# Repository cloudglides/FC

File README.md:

<h1 align="center">
  FC
  <br>
</h1>
<h4 align="center">
An STM32F405 flight controller
</h4>
<div align="center">

</div>
<p align="center">
  <a href="#key-features">Key Features</a> •
  <a href="#pcb">PCB</a> •
  <a href="#credits">Credits</a>
</p>

<p>&nbsp;</p>

# FC

FC is a 39 × 39 mm flight controller for multirotors, built around the STM32F405RGT6, with a 30.5 × 30.5 mm M3 mounting pattern.

it has a BMI270 gyro, a BMP388 barometer, 16 MB of blackbox flash and a 2S–6S power stage on one 4-layer board. connectors are JST-SH for a 4-in-1 ESC, receiver, HD VTX and GPS, plus USB-C.

to build your own, grab the KiCad files in `pcb/`, check the schematic and BOM, and send the Gerber files in `production/` to your preferred PCB manufacturer. the MCU can be flashed over USB (hold BOOT while plugging in) or through the SWD pads.

## Key Features

* **STM32F405RGT6** MCU, 168 MHz Cortex-M4
* **BMI270** 6-axis IMU on SPI
* **BMP388** barometer on I2C
* **W25Q128** 16 MB blackbox flash
* **2S–6S input** with an AP63205 5 V / 2 A buck and AP2112K 3.3 V regulator
* **USB-C** with ESD protection using USBLC6-2SC6
* **4 motor outputs**, ESC telemetry, battery voltage and current sensing
* **3 UARTs** broken out: receiver, HD VTX, GPS (with I2C for a compass)
* **Solder pads** for SWD, LED strip and buzzer
* **4-layer PCB** designed in KiCad, all parts available from LCSC

## PCB

designed in KiCad with a 4-layer stackup: signals on the outer layers, a solid ground plane and a 3.3 V plane inside.

the connectors sit on the board edges with the MCU in the centre. the gyro is right below the MCU's SPI pins, and the buck converter, regulator, flash and barometer are on the bottom side.

## Files

the repository includes the KiCad project files, schematics, BOM, Gerber exports and component placement files.

| Folder | Contents |
|---|---|
| `pcb/` | KiCad project, schematic, board, project symbol and footprint libraries |
| `docs/` | schematic PDF |
| `images/` | progress and final renders |
| `production/` | Gerber zip and pick-and-place file |
| `BOM.csv` | bill of materials with LCSC part numbers |
| `journal.md` | build log |
| `journals/` | the KiCad files and screenshots at each of the 15 design steps |
### Schematic

---

### PCB Layers

#### F.CU

#### B.CU

## PWR

## GND

---

### Board Views

#### Front

#### Back

### ZINE

## Credits

This project uses:
- [KiCad](https://www.kicad.org/)

## License

GPL

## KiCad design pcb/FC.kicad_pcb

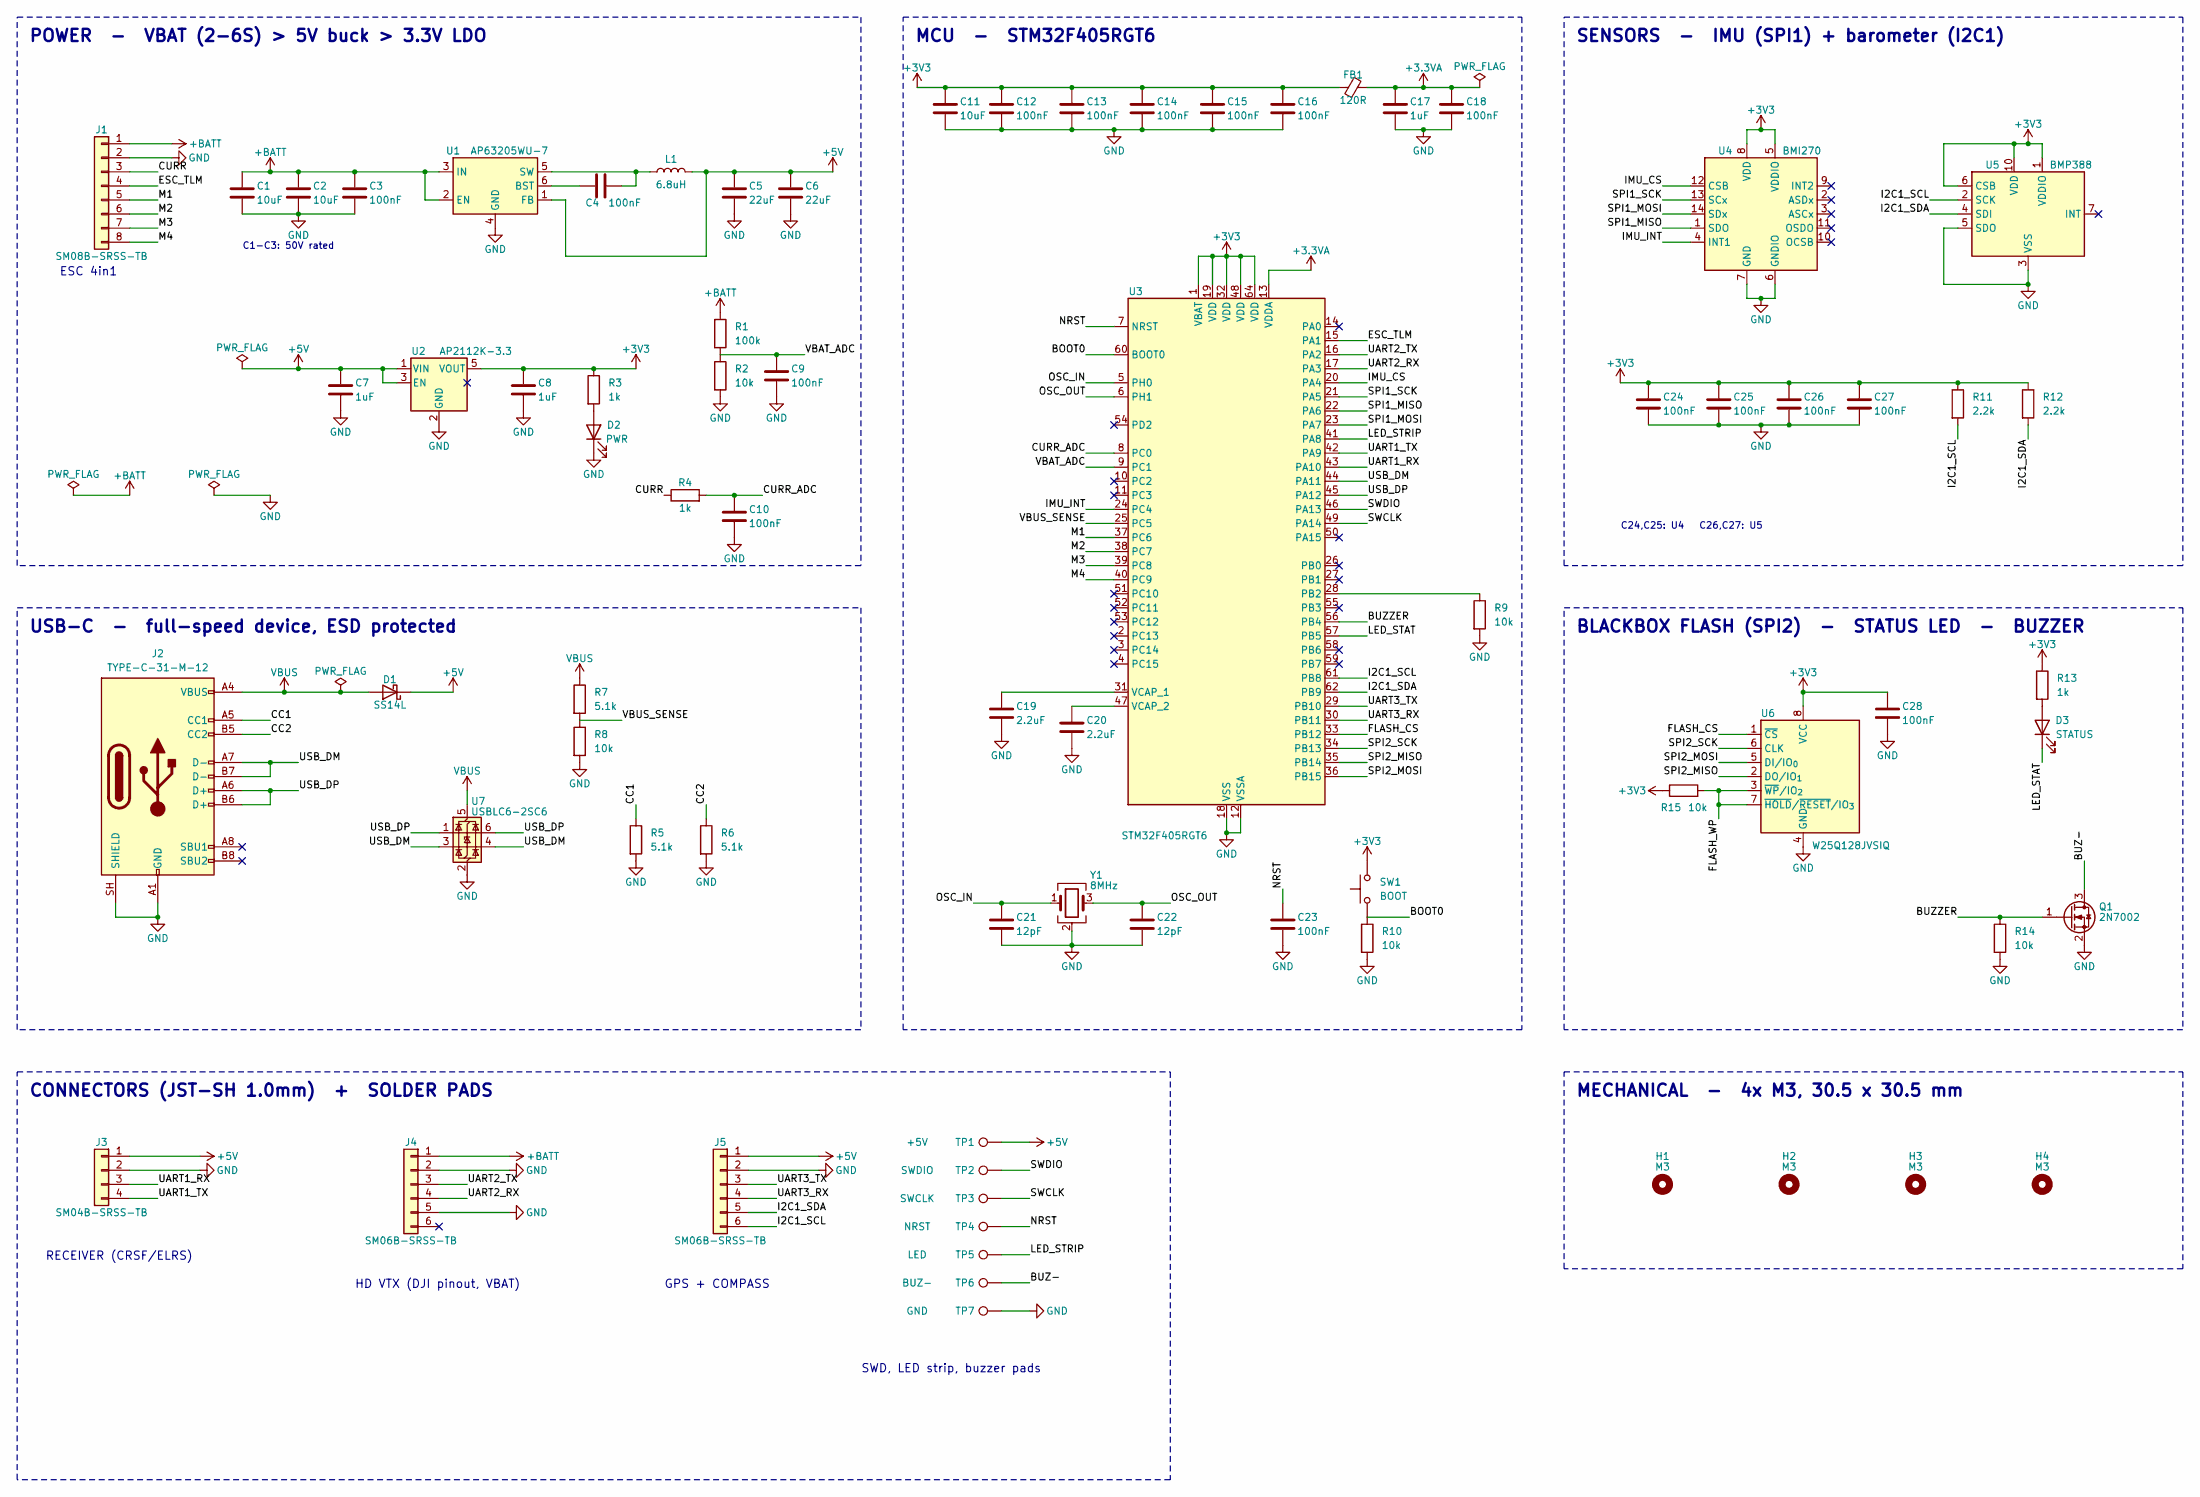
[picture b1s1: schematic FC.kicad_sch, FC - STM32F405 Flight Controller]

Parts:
C1, C2: 10uF; C_1206_3216Metric; MPN GRM31CR61H106KA12L; LCSC C77092
C3: 100nF; C_0603_1608Metric; MPN CC0603KRX7R9BB104; LCSC C14663
C4, C9, C10, C12, C13, C14, C15, C16, C18, C23, C24, C25, C26, C27, C28: 100nF; C_0402_1005Metric; MPN CL05B104KO5NNNC; LCSC C1525
C5, C6: 22uF; C_0805_2012Metric; MPN CL21A226MAQNNNE; LCSC C45783
C7, C8, C17: 1uF; C_0402_1005Metric; MPN CL05A105KA5NQNC; LCSC C52923
C11: 10uF; C_0603_1608Metric; MPN CL10A106KP8NNNC; LCSC C19702
C19, C20: 2.2uF; C_0402_1005Metric; MPN CL05A225MQ5NSNC; LCSC C12530
C21, C22: 12pF; C_0402_1005Metric; MPN 0402CG120J500NT; LCSC C1547
D1: SS14L; D_SOD-123F; MPN SS14L; LCSC C190475
D2: PWR; LED_0603_1608Metric; MPN KT-0603W; LCSC C2290
D3: STATUS; LED_0603_1608Metric; MPN XL-1608UBC-06A; LCSC C7371904
FB1: 120R; L_0603_1608Metric; MPN BLM18PG121SN1D; LCSC C14709
H1, H2, H3, H4: M3; MountingHole_3.2mm_M3
J1: SM08B-SRSS-TB; JST_SH_SM08B-SRSS-TB_1x08-1MP_P1.00mm_Horizontal; MPN SM08B-SRSS-TB(LF)(SN); LCSC C160407
J2: TYPE-C-31-M-12; USB_C_Receptacle_HRO_TYPE-C-31-M-12; MPN TYPE-C-31-M-12; LCSC C165948
J3: SM04B-SRSS-TB; JST_SH_SM04B-SRSS-TB_1x04-1MP_P1.00mm_Horizontal; MPN SM04B-SRSS-TB(LF)(SN); LCSC C160404
J4, J5: SM06B-SRSS-TB; JST_SH_SM06B-SRSS-TB_1x06-1MP_P1.00mm_Horizontal; MPN SM06B-SRSS-TB(LF)(SN); LCSC C160405
L1: 6.8uH; IND-SMD_L4.0-W4.0; MPN FHD4020S-6R8MT; LCSC C843301
Q1: 2N7002; SOT-23; MPN 2N7002; LCSC C8545
R1: 100k; R_0402_1005Metric; MPN 0402WGF1003TCE; LCSC C25741
R2, R8, R9, R10, R14, R15: 10k; R_0402_1005Metric; MPN RC0402FR-0710KL; LCSC C60490
R3, R4, R13: 1k; R_0402_1005Metric; MPN 0402WGF1001TCE; LCSC C11702
R5, R6, R7: 5.1k; R_0402_1005Metric; MPN 0402WGF5101TCE; LCSC C25905
R11, R12: 2.2k; R_0402_1005Metric; MPN 0402WGF2201TCE; LCSC C25879
SW1: BOOT; SW_Push_1P1T_XKB_TS-1187A; MPN TS-1187A-B-A-B; LCSC C318884
TP1: +5V; TestPoint_Pad_D1.5mm
TP2: SWDIO; TestPoint_Pad_D1.5mm
TP3: SWCLK; TestPoint_Pad_D1.5mm
TP4: NRST; TestPoint_Pad_D1.5mm
TP5: LED; TestPoint_Pad_D1.5mm
TP6: BUZ-; TestPoint_Pad_D1.5mm
TP7: GND; TestPoint_Pad_D1.5mm
U1: AP63205WU-7; TSOT-23-6; MPN AP63205WU-7; LCSC C2071056
U2: AP2112K-3.3; SOT-23-5; MPN AP2112K-3.3TRG1; LCSC C51118
U3: STM32F405RGT6; LQFP-64_10x10mm_P0.5mm; MPN STM32F405RGT6; LCSC C15742
U4: BMI270; LGA-14_L3.0-W2.5-P0.50-BR; MPN BMI270; LCSC C2836813
U5: BMP388; SENSORM-SMD_BMP388; MPN BMP388; LCSC C779278
U6: W25Q128JVSIQ; SOIC-8_5.3x5.3mm_P1.27mm; MPN W25Q128JVSIQ; LCSC C97521
U7: USBLC6-2SC6; SOT-23-6; MPN USBLC6-2SC6; LCSC C7519
Y1: 8MHz; Crystal_SMD_3225-4Pin_3.2x2.5mm; MPN XL2EL89CMI-111YLC-8M; LCSC C42388155

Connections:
+3.3VA: C17.1, C18.1, FB1.2, U3.13 (VDDA)
+3V3: C8.1, C11.1, C12.1, C13.1, C14.1, C15.1, C16.1, C24.1, C25.1, C26.1, C27.1, C28.1, FB1.1, R3.1, R11.1, R12.1, R13.1, R15.1, SW1.2, U2.5 (VOUT), U3.1 (VBAT), U3.19 (VDD), U3.32 (VDD), U3.48 (VDD), U3.64 (VDD), U4.5 (VDDIO), U4.8 (VDD), U5.1 (VDDIO), U5.6 (CSB), U5.10 (VDD), U6.8 (VCC)
+5V: C5.1, C6.1, C7.1, D1.1 (K), J3.1, J5.1, L1.2, TP1.1, U1.1 (FB), U2.1 (VIN), U2.3 (EN)
+BATT: C1.1, C2.1, C3.1, J1.1, J4.1, R1.1, U1.2 (EN), U1.3 (IN)
/BOOT0: R10.1, SW1.1, U3.60 (BOOT0)
/BUZ-: Q1.3 (D), TP6.1
/BUZZER: Q1.1 (G), R14.1, U3.56 (PB4)
/CC1: J2.A5 (CC1), R5.1
/CC2: J2.B5 (CC2), R6.1
/CURR: J1.3, R4.1
/CURR_ADC: C10.1, R4.2, U3.8 (PC0)
/ESC_TLM: J1.4, U3.15 (PA1)
/FLASH_CS: U3.33 (PB12), U6.1 (~CS)
/FLASH_WP: R15.2, U6.3 (~WP/IO_{2}), U6.7 (~HOLD/~RESET/IO_{3})
/I2C1_SCL: J5.6, R11.2, U3.61 (PB8), U5.2 (SCK)
/I2C1_SDA: J5.5, R12.2, U3.62 (PB9), U5.4 (SDI)
/IMU_CS: U3.20 (PA4), U4.12 (CSB)
/IMU_INT: U3.24 (PC4), U4.4 (INT1)
/LED_STAT: D3.1 (K), U3.57 (PB5)
/LED_STRIP: TP5.1, U3.41 (PA8)
/M1: J1.5, U3.37 (PC6)
/M2: J1.6, U3.38 (PC7)
/M3: J1.7, U3.39 (PC8)
/M4: J1.8, U3.40 (PC9)
/NRST: C23.1, TP4.1, U3.7 (NRST)
/OSC_IN: C21.1, U3.5 (PH0), Y1.1
/OSC_OUT: C22.1, U3.6 (PH1), Y1.3
/SPI1_MISO: U3.22 (PA6), U4.1 (SDO)
/SPI1_MOSI: U3.23 (PA7), U4.14 (SDx)
/SPI1_SCK: U3.21 (PA5), U4.13 (SCx)
/SPI2_MISO: U3.35 (PB14), U6.2 (DO/IO_{1})
/SPI2_MOSI: U3.36 (PB15), U6.5 (DI/IO_{0})
/SPI2_SCK: U3.34 (PB13), U6.6 (CLK)
/SWCLK: TP3.1, U3.49 (PA14)
/SWDIO: TP2.1, U3.46 (PA13)
/UART1_RX: J3.3, U3.43 (PA10)
/UART1_TX: J3.4, U3.42 (PA9)
/UART2_RX: J4.4, U3.17 (PA3)
/UART2_TX: J4.3, U3.16 (PA2)
/UART3_RX: J5.4, U3.30 (PB11)
/UART3_TX: J5.3, U3.29 (PB10)
/USB_DM: J2.A7 (D-), J2.B7 (D-), U3.44 (PA11), U7.3 (I/O2), U7.4 (I/O2)
/USB_DP: J2.A6 (D+), J2.B6 (D+), U3.45 (PA12), U7.1 (I/O1), U7.6 (I/O1)
/VBAT_ADC: C9.1, R1.2, R2.1, U3.9 (PC1)
/VBUS_SENSE: R7.2, R8.1, U3.25 (PC5)
GND: C1.2, C2.2, C3.2, C5.2, C6.2, C7.2, C8.2, C9.2, C10.2, C11.2, C12.2, C13.2, C14.2, C15.2, C16.2, C17.2, C18.2, C19.2, C20.2, C21.2, C22.2, C23.2, C24.2, C25.2, C26.2, C27.2, C28.2, D2.1 (K), J1.2, J2.A1 (GND), J2.A12 (GND), J2.B1 (GND), J2.B12 (GND), J2.SH (SHIELD), J3.2, J4.2, J4.5, J5.2, Q1.2 (S), R2.2, R5.2, R6.2, R8.2, R9.2, R10.2, R14.2, TP7.1, U1.4 (GND), U2.2 (GND), U3.12 (VSSA), U3.18 (VSS), U3.63 (VSS), U4.6 (GNDIO), U4.7 (GND), U5.3 (VSS), U5.5 (SDO), U5.8 (VSS), U5.9 (VSS), U6.4 (GND), U7.2 (GND), Y1.2 (G), Y1.4 (G)
unnamed: D2.2 (A), R3.2
unnamed: D3.2 (A), R13.2
unnamed: C4.1, U1.6 (BST)
unnamed: C4.2, L1.1, U1.5 (SW)
unnamed: R9.1, U3.28 (PB2)
unnamed: C19.1, U3.31 (VCAP_1)
unnamed: C20.1, U3.47 (VCAP_2)
VBUS: D1.2 (A), J2.A4 (VBUS), J2.A9 (VBUS), J2.B4 (VBUS), J2.B9 (VBUS), R7.1, U7.5 (VBUS)

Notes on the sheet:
POWER - VBAT (2-6S) > 5V buck > 3.3V LDO
ESC 4in1
C1-C3: 50V rated
USB-C - full-speed device, ESD protected
MCU - STM32F405RGT6
SENSORS - IMU (SPI1) + barometer (I2C1)
C24,C25: U4 C26,C27: U5
BLACKBOX FLASH (SPI2) - STATUS LED - BUZZER
CONNECTORS (JST-SH 1.0mm) + SOLDER PADS
RECEIVER (CRSF/ELRS)
HD VTX (DJI pinout, VBAT)
GPS + COMPASS
SWD, LED strip, buzzer pads
MECHANICAL - 4x M3, 30.5 x 30.5 mm

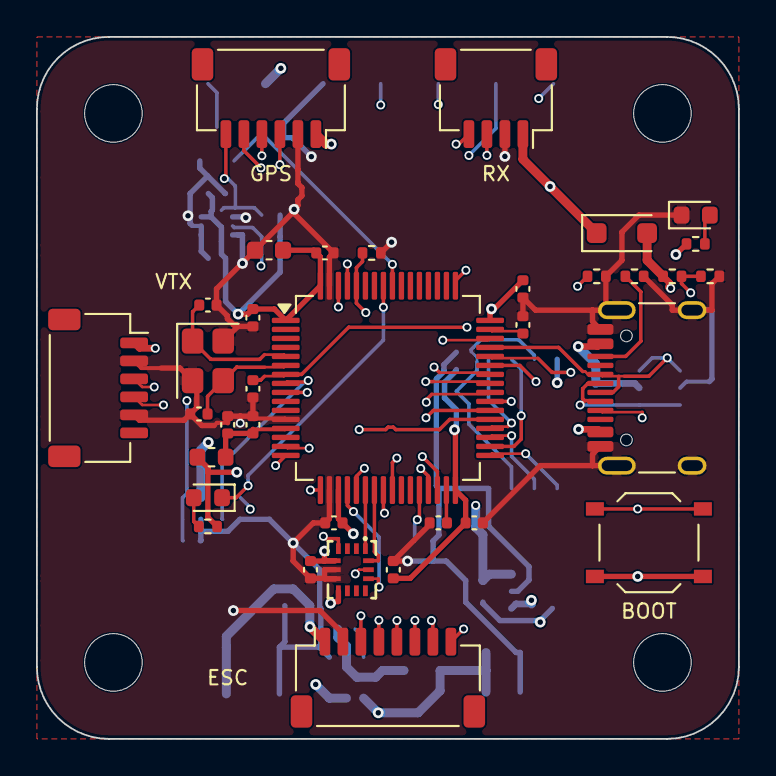
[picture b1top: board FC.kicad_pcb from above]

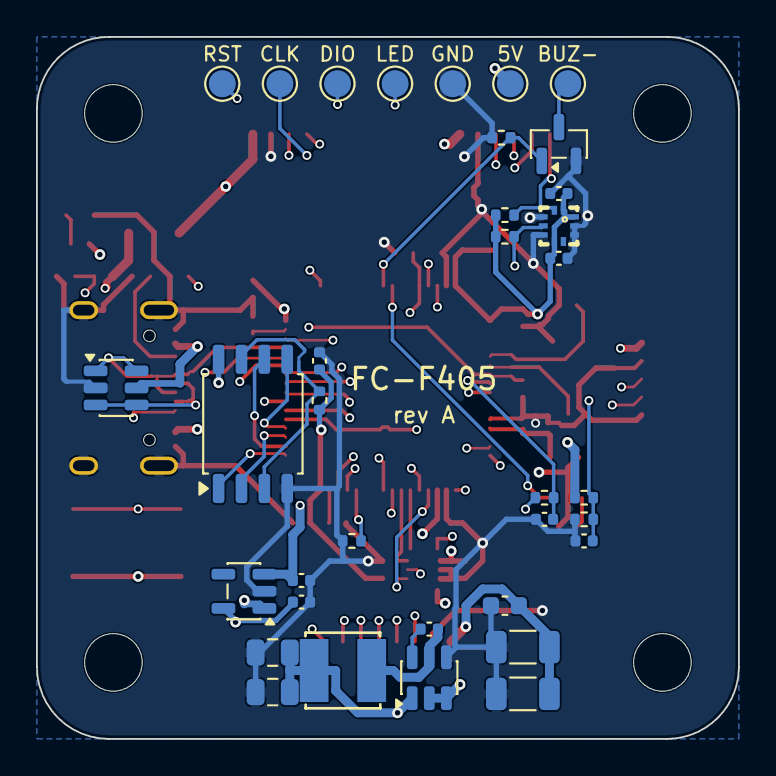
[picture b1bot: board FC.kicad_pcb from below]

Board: 4 copper layers, 39.0 x 39.0 mm, 74 parts (35 on the bottom side), 54 nets.

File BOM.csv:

Comment,Designator,Footprint,LCSC Part #,Quantity
10uF,"C1,C2",C_1206_3216Metric,C77092,2
100nF,C3,C_0603_1608Metric,C14663,1
100nF,"C4,C9,C10,C12,C13,C14,C15,C16,C18,C23,C24,C25,C26,C27,C28",C_0402_1005Metric,C1525,15
22uF,"C5,C6",C_0805_2012Metric,C45783,2
1uF,"C7,C8,C17",C_0402_1005Metric,C52923,3
10uF,C11,C_0603_1608Metric,C19702,1
2.2uF,"C19,C20",C_0402_1005Metric,C12530,2
12pF,"C21,C22",C_0402_1005Metric,C1547,2
SS14L,D1,D_SOD-123F,C190475,1
PWR,D2,LED_0603_1608Metric,C2290,1
STATUS,D3,LED_0603_1608Metric,C7371904,1
120R,FB1,L_0603_1608Metric,C14709,1
SM08B-SRSS-TB,J1,JST_SH_SM08B-SRSS-TB_1x08-1MP_P1.00mm_Horizontal,C160407,1
TYPE-C-31-M-12,J2,USB_C_Receptacle_HRO_TYPE-C-31-M-12,C165948,1
SM04B-SRSS-TB,J3,JST_SH_SM04B-SRSS-TB_1x04-1MP_P1.00mm_Horizontal,C160404,1
SM06B-SRSS-TB,"J4,J5",JST_SH_SM06B-SRSS-TB_1x06-1MP_P1.00mm_Horizontal,C160405,2
6.8uH,L1,IND-SMD_L4.0-W4.0,C843301,1
2N7002,Q1,SOT-23,C8545,1
100k,R1,R_0402_1005Metric,C25741,1
10k,"R2,R8,R9,R10,R14,R15",R_0402_1005Metric,C60490,6
1k,"R3,R4,R13",R_0402_1005Metric,C11702,3
5.1k,"R5,R6,R7",R_0402_1005Metric,C25905,3
2.2k,"R11,R12",R_0402_1005Metric,C25879,2
BOOT,SW1,SW_Push_1P1T_XKB_TS-1187A,C318884,1
AP63205WU-7,U1,TSOT-23-6,C2071056,1
AP2112K-3.3,U2,SOT-23-5,C51118,1
STM32F405RGT6,U3,LQFP-64_10x10mm_P0.5mm,C15742,1
BMI270,U4,LGA-14_L3.0-W2.5-P0.50-BR,C2836813,1
BMP388,U5,SENSORM-SMD_BMP388,C779278,1
W25Q128JVSIQ,U6,SOIC-8_5.3x5.3mm_P1.27mm,C97521,1
USBLC6-2SC6,U7,SOT-23-6,C7519,1
8MHz,Y1,Crystal_SMD_3225-4Pin_3.2x2.5mm,C42388155,1
